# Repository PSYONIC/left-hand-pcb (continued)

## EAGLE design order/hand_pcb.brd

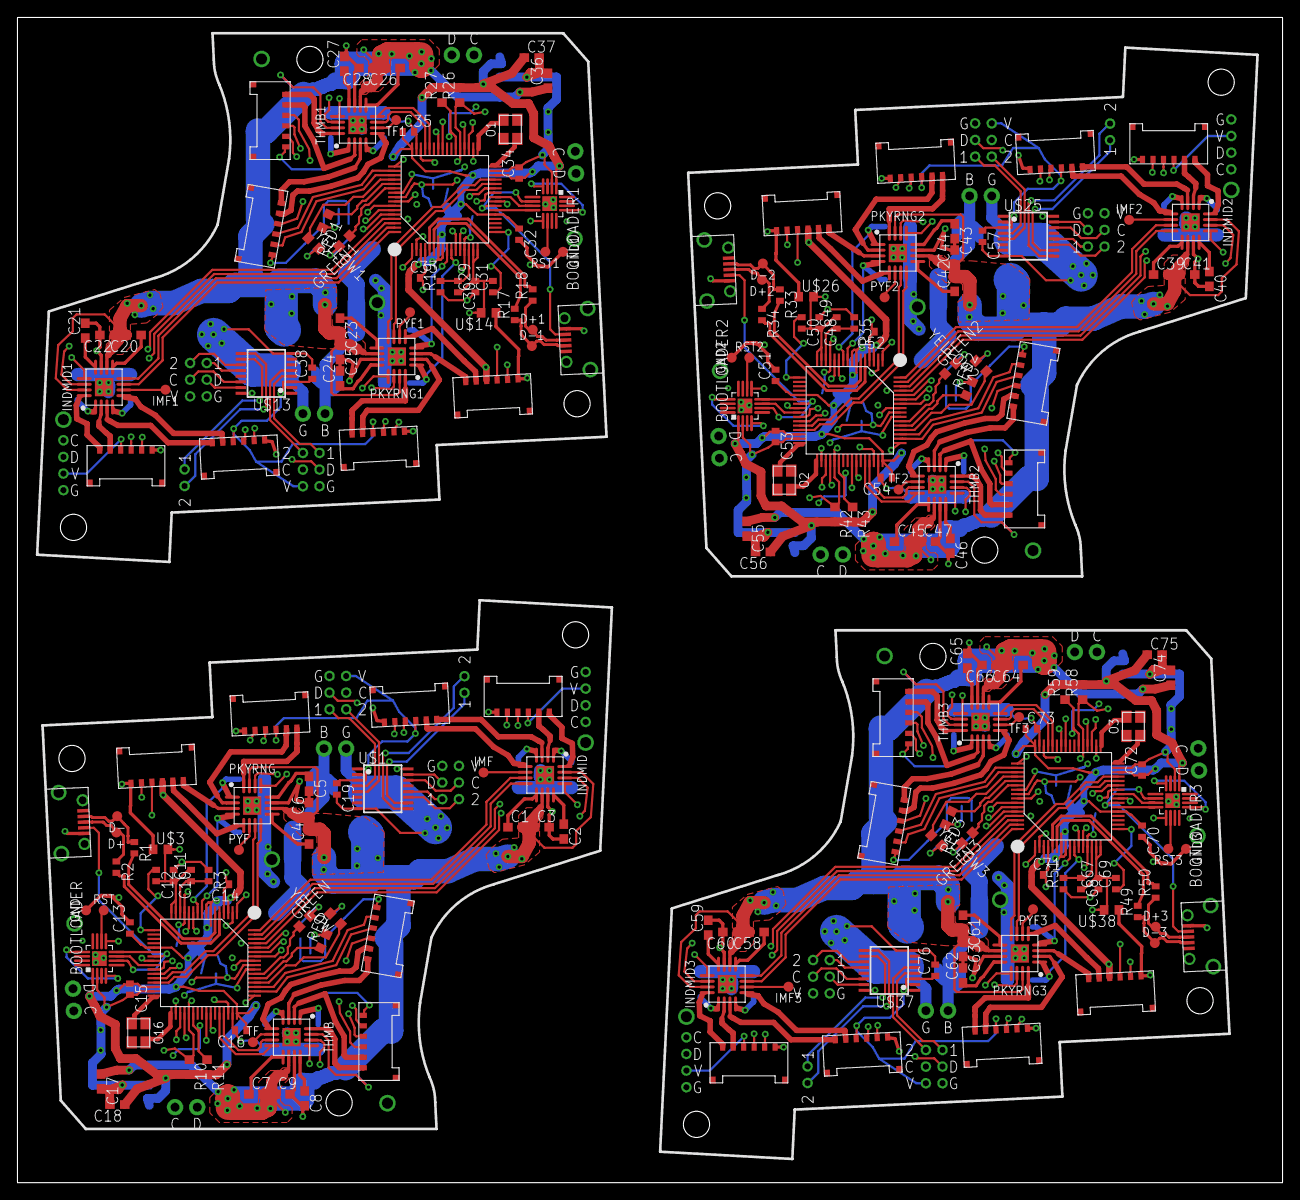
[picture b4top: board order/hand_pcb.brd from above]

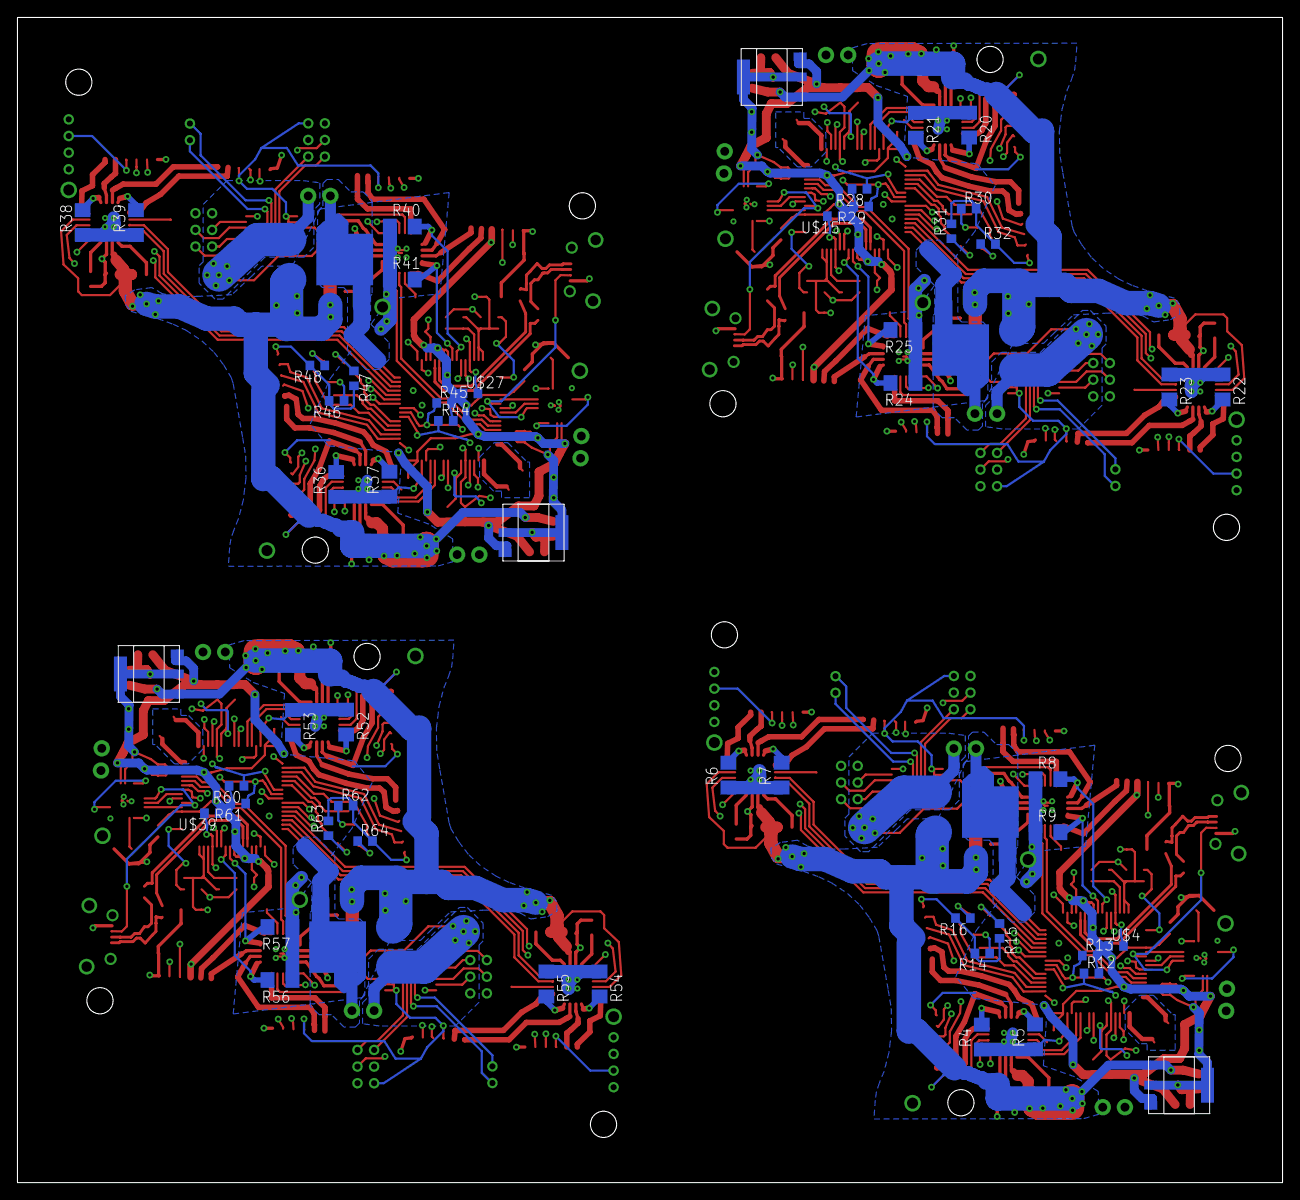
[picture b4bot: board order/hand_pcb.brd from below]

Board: 4 copper layers, 144.8 x 133.3 mm, 280 parts (56 on the bottom side), 348 nets.

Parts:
BOOTLOADER, BOOTLOADER1, BOOTLOADER2, BOOTLOADER3: MKL02Z32CORRECT; QFN16
C1, C4, C7, C20, C23, C26, C39, C42, C45, C58, C61, C64: 0.01; C0603
C2, C5, C8, C21, C24, C27, C40, C43, C46, C59, C62, C65: 2.2; C0603
C3, C6, C9, C22, C25, C28, C41, C44, C47, C60, C63, C66: 10; C0603
C10, C29, C48, C67: 2.2; C0402
C11, C12, C13, C14, C15, C16, C19, C30, C31, C32, C33, C34, C35, C38, C49, C50, C51, C52, C53, C54, C57, C68, C69, C70, C71, C72, C73, C76: 0.1; C0402
C17, C18, C36, C37, C55, C56, C74, C75: C0603
D+, D+1, D+2, D+3: TESTPAD
D-, D-1, D-2, D-3: TESTPAD
GND, GND1, GND2, GND3: TESTPAD
GREEN, GREEN1, GREEN2, GREEN3: LED0603; L0603
HAND_MICRO, HAND_MICRO1, HAND_MICRO2, HAND_MICRO3: MK20DX256VLH7; LQFP-64-10-10
IMF, IMF1, IMF2, IMF3: TESTPAD
INDEX, INDEX1, INDEX2, INDEX3: DF57H-6PTOP; DF57H-6P-TOP
INDMID, INDMID1, INDMID2, INDMID3: DRV8833; WQFN-16
MIDDLE, MIDDLE1, MIDDLE2, MIDDLE3: DF57H-6PTOP; DF57H-6P-TOP
O1, O2, O3, O16: 16MHz; NX3225SA
PINKY, PINKY1, PINKY2, PINKY3: DF57H-6PTOP; DF57H-6P-TOP
PKYRNG, PKYRNG1, PKYRNG2, PKYRNG3: DRV8833; WQFN-16
PYF, PYF1, PYF2, PYF3: TESTPAD
R1, R2, R17, R18, R33, R34, R49, R50: 33; R0402
R3, R19, R35, R51: 470; R0402
R4, R5, R6, R7, R8, R9, R20, R21, R22, R23, R24, R25, R36, R37, R38, R39, R40, R41, R52, R53, R54, R55, R56, R57: 0.2; R1206
R10, R11, R12, R13, R26, R27, R28, R29, R42, R43, R44, R45, R58, R59, R60, R61: 1k; R0603
R14, R30, R46, R62: 100; R0603
R15, R16, R31, R32, R47, R48, R63, R64: 200; R0603
RED, RED1, RED2, RED3: LED0603; L0603
RING, RING1, RING2, RING3: DF57H-6PTOP; DF57H-6P-TOP
RST, RST1, RST2, RST3: TESTPAD
TF, TF1, TF2, TF3: TESTPAD
THMB, THMB1, THMB2, THMB3: DRV8833; WQFN-16
THUMB_A, THUMB_A1, THUMB_A2, THUMB_A3: DF57H-6PTOP; DF57H-6P-TOP
THUMB_B, THUMB_B1, THUMB_B2, THUMB_B3: DF57H-6PTOP; DF57H-6P-TOP
U$1, U$13, U$25, U$37: TCA9534TSSOP; TSSOP16
U$2, U$16, U$28, U$40: SPD15P10PLG; PG-TO-252-3
U$3, U$4, U$14, U$15, U$26, U$27, U$38, U$39: L0603
U$5, U$7, U$17, U$18, U$29, U$30, U$41, U$42: PSENSE
U$6, U$19, U$31, U$43: PSENSE2
U$8, U$20, U$32, U$44: PSENSE4
U$9, U$21, U$33, U$45: MIC391003.3; MIC39100
U$10, U$22, U$34, U$46: THRUHOLE2
U$11, U$12, U$23, U$24, U$35, U$36, U$47, U$48: THRUHOLEI2C
USB, USB1, USB2, USB3: 10118194-0001LF
YELLOW, YELLOW1, YELLOW2, YELLOW3: LED0603; L0603

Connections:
+3V1: BOOTLOADER1.1, C32.1, C33.1, C34.1, C35.1, C37.1, C38.1, HAND_MICRO1.3, HAND_MICRO1.7, HAND_MICRO1.8, HAND_MICRO1.21, HAND_MICRO1.30, HAND_MICRO1.48, INDEX1.3, MIDDLE1.3, PINKY1.3, R26.2, R27.2, R28.2, R29.2, RING1.3, THUMB_A1.3, THUMB_B1.3, U$13.1, U$13.2, U$13.3, U$13.16, U$15.1, U$17.V, U$18.V, U$20.V, U$21.3
+3V2: BOOTLOADER2.1, C51.1, C52.1, C53.1, C54.1, C56.1, C57.1, HAND_MICRO2.3, HAND_MICRO2.7, HAND_MICRO2.8, HAND_MICRO2.21, HAND_MICRO2.30, HAND_MICRO2.48, INDEX2.3, MIDDLE2.3, PINKY2.3, R42.2, R43.2, R44.2, R45.2, RING2.3, THUMB_A2.3, THUMB_B2.3, U$25.1, U$25.2, U$25.3, U$25.16, U$27.1, U$29.V, U$30.V, U$32.V, U$33.3
+3V3: BOOTLOADER.1, C13.1, C14.1, C15.1, C16.1, C18.1, C19.1, HAND_MICRO.3, HAND_MICRO.7, HAND_MICRO.8, HAND_MICRO.21, HAND_MICRO.30, HAND_MICRO.48, INDEX.3, MIDDLE.3, PINKY.3, R10.2, R11.2, R12.2, R13.2, RING.3, THUMB_A.3, THUMB_B.3, U$1.1, U$1.2, U$1.3, U$1.16, U$4.1, U$5.V, U$7.V, U$8.V, U$9.3
+3V4: BOOTLOADER3.1, C70.1, C71.1, C72.1, C73.1, C75.1, C76.1, HAND_MICRO3.3, HAND_MICRO3.7, HAND_MICRO3.8, HAND_MICRO3.21, HAND_MICRO3.30, HAND_MICRO3.48, INDEX3.3, MIDDLE3.3, PINKY3.3, R58.2, R59.2, R60.2, R61.2, RING3.3, THUMB_A3.3, THUMB_B3.3, U$37.1, U$37.2, U$37.3, U$37.16, U$39.1, U$41.V, U$42.V, U$44.V, U$45.3
+5V: C1.2, C3.1, C4.2, C6.1, C7.2, C9.1, C17.1, INDMID.10, INDMID.15, PKYRNG.10, PKYRNG.15, THMB.10, THMB.15, U$2.3, U$9.1
+5V1: C20.2, C22.1, C23.2, C25.1, C26.2, C28.1, C36.1, INDMID1.10, INDMID1.15, PKYRNG1.10, PKYRNG1.15, THMB1.10, THMB1.15, U$16.3, U$21.1
+5V2: C39.2, C41.1, C42.2, C44.1, C45.2, C47.1, C55.1, INDMID2.10, INDMID2.15, PKYRNG2.10, PKYRNG2.15, THMB2.10, THMB2.15, U$28.3, U$33.1
+5V3: C58.2, C60.1, C61.2, C63.1, C64.2, C66.1, C74.1, INDMID3.10, INDMID3.15, PKYRNG3.10, PKYRNG3.15, THMB3.10, THMB3.15, U$40.3, U$45.1
EN1: U$1.4, U$5.1
EN2: U$1.5, U$5.2
EN3: U$1.12, U$7.1
EN4: U$1.11, U$7.2
EN5: U$1.10, U$6.1
EN6: U$1.9, U$6.2
EN7: U$13.4, U$17.1
EN8: U$13.5, U$17.2
EN9: U$13.9, U$19.2
EN10: U$13.12, U$18.1
EN11: U$13.11, U$18.2
EN12: U$13.10, U$19.1
EN13: U$25.4, U$29.1
EN14: U$25.5, U$29.2
EN15: U$25.9, U$31.2
EN16: U$25.12, U$30.1
EN17: U$25.11, U$30.2
EN18: U$25.10, U$31.1
EN19: U$37.4, U$41.1
EN20: U$37.5, U$41.2
EN21: U$37.9, U$43.2
EN22: U$37.12, U$42.1
EN23: U$37.11, U$42.2
EN24: U$37.10, U$43.1
GND: BOOTLOADER.2, BOOTLOADER.TH, C2.2, C3.2, C5.2, C6.2, C8.2, C9.2, C13.2, C14.2, C15.2, C16.2, C17.2, C18.2, C19.2, GND.P$1, HAND_MICRO.4, HAND_MICRO.31, HAND_MICRO.47, INDEX.6, INDMID.11, INDMID.PPAD, MIDDLE.6, PINKY.6, PKYRNG.11, PKYRNG.PPAD, R4.1, R5.1, R6.1, R7.1, R8.1, R9.1, R14.2, R15.2, R16.2, RING.6, THMB.11, THMB.PPAD, THUMB_A.6, THUMB_B.6, U$1.8, U$2.1, U$3.1, U$5.G, U$7.G, U$8.G, U$9.2, U$9.TAB, U$10.G, USB.5
GND1: BOOTLOADER1.2, BOOTLOADER1.TH, C21.2, C22.2, C24.2, C25.2, C27.2, C28.2, C32.2, C33.2, C34.2, C35.2, C36.2, C37.2, C38.2, GND1.P$1, HAND_MICRO1.4, HAND_MICRO1.31, HAND_MICRO1.47, INDEX1.6, INDMID1.11, INDMID1.PPAD, MIDDLE1.6, PINKY1.6, PKYRNG1.11, PKYRNG1.PPAD, R20.1, R21.1, R22.1, R23.1, R24.1, R25.1, R30.2, R31.2, R32.2, RING1.6, THMB1.11, THMB1.PPAD, THUMB_A1.6, THUMB_B1.6, U$13.8, U$14.1, U$16.1, U$17.G, U$18.G, U$20.G, U$21.2, U$21.TAB, U$22.G, USB1.5
GND2: BOOTLOADER2.2, BOOTLOADER2.TH, C40.2, C41.2, C43.2, C44.2, C46.2, C47.2, C51.2, C52.2, C53.2, C54.2, C55.2, C56.2, C57.2, GND2.P$1, HAND_MICRO2.4, HAND_MICRO2.31, HAND_MICRO2.47, INDEX2.6, INDMID2.11, INDMID2.PPAD, MIDDLE2.6, PINKY2.6, PKYRNG2.11, PKYRNG2.PPAD, R36.1, R37.1, R38.1, R39.1, R40.1, R41.1, R46.2, R47.2, R48.2, RING2.6, THMB2.11, THMB2.PPAD, THUMB_A2.6, THUMB_B2.6, U$25.8, U$26.1, U$28.1, U$29.G, U$30.G, U$32.G, U$33.2, U$33.TAB, U$34.G, USB2.5
GND3: BOOTLOADER3.2, BOOTLOADER3.TH, C59.2, C60.2, C62.2, C63.2, C65.2, C66.2, C70.2, C71.2, C72.2, C73.2, C74.2, C75.2, C76.2, GND3.P$1, HAND_MICRO3.4, HAND_MICRO3.31, HAND_MICRO3.47, INDEX3.6, INDMID3.11, INDMID3.PPAD, MIDDLE3.6, PINKY3.6, PKYRNG3.11, PKYRNG3.PPAD, R52.1, R53.1, R54.1, R55.1, R56.1, R57.1, R62.2, R63.2, R64.2, RING3.6, THMB3.11, THMB3.PPAD, THUMB_A3.6, THUMB_B3.6, U$37.8, U$38.1, U$40.1, U$41.G, U$42.G, U$44.G, U$45.2, U$45.TAB, U$46.G, USB3.5
IDX1: INDEX.1, INDMID.16
IDX2: INDEX.2, INDMID.2
IDX3: INDEX1.1, INDMID1.16
IDX4: INDEX1.2, INDMID1.2
IDX5: INDEX2.1, INDMID2.16
IDX6: INDEX2.2, INDMID2.2
IDX7: INDEX3.1, INDMID3.16
IDX8: INDEX3.2, INDMID3.2
IDXENC1: HAND_MICRO.58, INDEX.5
IDXENC2: HAND_MICRO.57, INDEX.4
IDXENC3: HAND_MICRO1.57, INDEX1.4
IDXENC4: HAND_MICRO1.58, INDEX1.5
IDXENC5: HAND_MICRO2.57, INDEX2.4
IDXENC6: HAND_MICRO2.58, INDEX2.5
IDXENC7: HAND_MICRO3.57, INDEX3.4
IDXENC8: HAND_MICRO3.58, INDEX3.5
IDXISEN: INDMID.1, R6.2
IDXISEN1: INDMID1.1, R22.2
IDXISEN2: INDMID2.1, R38.2
IDXISEN3: INDMID3.1, R54.2
IDXPWM1: HAND_MICRO.61, INDMID.14
IDXPWM2: HAND_MICRO.62, INDMID.13
IDXPWM3: HAND_MICRO1.62, INDMID1.13
IDXPWM4: HAND_MICRO1.61, INDMID1.14
IDXPWM5: HAND_MICRO2.62, INDMID2.13
IDXPWM6: HAND_MICRO2.61, INDMID2.14
IDXPWM7: HAND_MICRO3.62, INDMID3.13
IDXPWM8: HAND_MICRO3.61, INDMID3.14
LED0: HAND_MICRO.53, RED.1
LED1: GREEN.1, HAND_MICRO.54
LED2: HAND_MICRO.52, YELLOW.1
LED3: HAND_MICRO1.53, RED1.1
LED4: GREEN1.1, HAND_MICRO1.54
LED5: HAND_MICRO1.52, YELLOW1.1
LED6: HAND_MICRO2.53, RED2.1
LED7: GREEN2.1, HAND_MICRO2.54
LED8: HAND_MICRO2.52, YELLOW2.1
LED9: HAND_MICRO3.53, RED3.1
LED10: GREEN3.1, HAND_MICRO3.54
LED11: HAND_MICRO3.52, YELLOW3.1
MID1: INDMID.5, MIDDLE.2
MID2: INDMID.3, MIDDLE.1
MID3: INDMID1.3, MIDDLE1.1
MID4: INDMID1.5, MIDDLE1.2
MID5: INDMID2.3, MIDDLE2.1
MID6: INDMID2.5, MIDDLE2.2
MID7: INDMID3.3, MIDDLE3.1
MID8: INDMID3.5, MIDDLE3.2
MIDENC1: HAND_MICRO.60, MIDDLE.5
MIDENC2: HAND_MICRO.59, MIDDLE.4
MIDENC3: HAND_MICRO1.59, MIDDLE1.4
MIDENC4: HAND_MICRO1.60, MIDDLE1.5
MIDENC5: HAND_MICRO2.59, MIDDLE2.4
MIDENC6: HAND_MICRO2.60, MIDDLE2.5
MIDENC7: HAND_MICRO3.59, MIDDLE3.4
MIDENC8: HAND_MICRO3.60, MIDDLE3.5
MIDISEN: INDMID.4, R7.2
MIDISEN1: INDMID1.4, R23.2
MIDISEN2: INDMID2.4, R39.2
MIDISEN3: INDMID3.4, R55.2
MIDPWM1: HAND_MICRO.64, INDMID.7
MIDPWM2: HAND_MICRO.63, INDMID.8
MIDPWM3: HAND_MICRO1.63, INDMID1.8
MIDPWM4: HAND_MICRO1.64, INDMID1.7
MIDPWM5: HAND_MICRO2.63, INDMID2.8
MIDPWM6: HAND_MICRO2.64, INDMID2.7
MIDPWM7: HAND_MICRO3.63, INDMID3.8
MIDPWM8: HAND_MICRO3.64, INDMID3.7
unnamed: R14.1, RED.2
unnamed: GREEN.2, R15.1
unnamed: R16.1, YELLOW.2
unnamed: IMF.P$1, INDMID.6
unnamed: PKYRNG.6, PYF.P$1
unnamed: TF.P$1, THMB.6
unnamed: C10.1, HAND_MICRO.13, R3.1, U$4.2
unnamed: BOOTLOADER.9, HAND_MICRO.24
unnamed: C11.1, HAND_MICRO.14, R3.2
unnamed: BOOTLOADER.8, HAND_MICRO.22
unnamed: BOOTLOADER.7, HAND_MICRO.25
unnamed: BOOTLOADER.10, RST.P$1
unnamed: BOOTLOADER1.4, BOOTLOADER1.13, HAND_MICRO1.34
unnamed: C29.2, C30.2, C31.2, HAND_MICRO1.15, HAND_MICRO1.16, U$14.2
unnamed: C20.1, INDMID1.9
unnamed: C23.1, PKYRNG1.9
unnamed: BOOTLOADER.4, BOOTLOADER.13, HAND_MICRO.34
unnamed: C10.2, C11.2, C12.2, HAND_MICRO.15, HAND_MICRO.16, U$3.2
unnamed: C26.1, THMB1.9
unnamed: C27.1, THMB1.12
unnamed: C1.1, INDMID.9
unnamed: C4.1, PKYRNG.9
unnamed: C7.1, THMB.9
unnamed: HAND_MICRO.33, O16.3
unnamed: C8.1, THMB.12
unnamed: C5.1, PKYRNG.12
unnamed: C2.1, INDMID.12
unnamed: HAND_MICRO.32, O16.1
unnamed: C24.1, PKYRNG1.12
unnamed: C21.1, INDMID1.12
unnamed: HAND_MICRO1.33, O1.3
unnamed: HAND_MICRO1.32, O1.1
unnamed: C31.1, HAND_MICRO1.17
unnamed: C12.1, HAND_MICRO.17
unnamed: BOOTLOADER.6, HAND_MICRO.23, USB.4
unnamed: BOOTLOADER1.6, HAND_MICRO1.23, USB1.4
unnamed: R30.1, RED1.2
unnamed: GREEN1.2, R31.1
unnamed: R32.1, YELLOW1.2
unnamed: IMF1.P$1, INDMID1.6
unnamed: PKYRNG1.6, PYF1.P$1
unnamed: TF1.P$1, THMB1.6
unnamed: C29.1, HAND_MICRO1.13, R19.1, U$15.2
unnamed: C30.1, HAND_MICRO1.14, R19.2
unnamed: BOOTLOADER1.9, HAND_MICRO1.24
unnamed: BOOTLOADER1.8, HAND_MICRO1.22
unnamed: BOOTLOADER1.7, HAND_MICRO1.25
unnamed: BOOTLOADER1.10, RST1.P$1
unnamed: BOOTLOADER2.4, BOOTLOADER2.13, HAND_MICRO2.34
unnamed: C48.2, C49.2, C50.2, HAND_MICRO2.15, HAND_MICRO2.16, U$26.2
unnamed: C39.1, INDMID2.9
unnamed: C42.1, PKYRNG2.9
unnamed: C45.1, THMB2.9
unnamed: C46.1, THMB2.12
unnamed: C43.1, PKYRNG2.12
unnamed: C40.1, INDMID2.12
unnamed: HAND_MICRO2.33, O2.3
unnamed: HAND_MICRO2.32, O2.1
unnamed: C50.1, HAND_MICRO2.17
unnamed: BOOTLOADER2.6, HAND_MICRO2.23, USB2.4
unnamed: R46.1, RED2.2
unnamed: GREEN2.2, R47.1
unnamed: R48.1, YELLOW2.2
unnamed: IMF2.P$1, INDMID2.6
unnamed: PKYRNG2.6, PYF2.P$1
unnamed: TF2.P$1, THMB2.6
unnamed: C48.1, HAND_MICRO2.13, R35.1, U$27.2
unnamed: C49.1, HAND_MICRO2.14, R35.2
unnamed: BOOTLOADER2.9, HAND_MICRO2.24
unnamed: BOOTLOADER2.8, HAND_MICRO2.22
unnamed: BOOTLOADER2.7, HAND_MICRO2.25
unnamed: BOOTLOADER2.10, RST2.P$1
unnamed: BOOTLOADER3.4, BOOTLOADER3.13, HAND_MICRO3.34
unnamed: C67.2, C68.2, C69.2, HAND_MICRO3.15, HAND_MICRO3.16, U$38.2
unnamed: C58.1, INDMID3.9
unnamed: C61.1, PKYRNG3.9
unnamed: C64.1, THMB3.9
unnamed: C65.1, THMB3.12
unnamed: C62.1, PKYRNG3.12
unnamed: C59.1, INDMID3.12
unnamed: HAND_MICRO3.33, O3.3
unnamed: HAND_MICRO3.32, O3.1
unnamed: C69.1, HAND_MICRO3.17
unnamed: BOOTLOADER3.6, HAND_MICRO3.23, USB3.4
unnamed: R62.1, RED3.2
unnamed: GREEN3.2, R63.1
unnamed: R64.1, YELLOW3.2
unnamed: IMF3.P$1, INDMID3.6
unnamed: PKYRNG3.6, PYF3.P$1
unnamed: TF3.P$1, THMB3.6
unnamed: C67.1, HAND_MICRO3.13, R51.1, U$39.2
unnamed: C68.1, HAND_MICRO3.14, R51.2
unnamed: BOOTLOADER3.9, HAND_MICRO3.24
unnamed: BOOTLOADER3.8, HAND_MICRO3.22
unnamed: BOOTLOADER3.7, HAND_MICRO3.25
unnamed: BOOTLOADER3.10, RST3.P$1
PKY1: PINKY.2, PKYRNG.5
PKY2: PINKY.1, PKYRNG.3
PKY3: PINKY1.2, PKYRNG1.5
PKY4: PINKY1.1, PKYRNG1.3
PKY5: PINKY2.2, PKYRNG2.5
PKY6: PINKY2.1, PKYRNG2.3
PKY7: PINKY3.2, PKYRNG3.5
PKY8: PINKY3.1, PKYRNG3.3
PKYENC1: HAND_MICRO.26, PINKY.5
PKYENC2: HAND_MICRO.27, PINKY.4
PKYENC3: HAND_MICRO1.26, PINKY1.5
PKYENC4: HAND_MICRO1.27, PINKY1.4
PKYENC5: HAND_MICRO2.26, PINKY2.5
PKYENC6: HAND_MICRO2.27, PINKY2.4
PKYENC7: HAND_MICRO3.26, PINKY3.5
PKYENC8: HAND_MICRO3.27, PINKY3.4
PKYISEN: HAND_MICRO.9, PKYRNG.4, R9.2
PKYISEN1: HAND_MICRO1.9, PKYRNG1.4, R25.2
PKYISEN2: HAND_MICRO2.9, PKYRNG2.4, R41.2
PKYISEN3: HAND_MICRO3.9, PKYRNG3.4, R57.2
PKYPWM1: HAND_MICRO.28, PKYRNG.7
PKYPWM2: HAND_MICRO.29, PKYRNG.8
PKYPWM3: HAND_MICRO1.29, PKYRNG1.8
PKYPWM4: HAND_MICRO1.28, PKYRNG1.7
PKYPWM5: HAND_MICRO2.29, PKYRNG2.8
PKYPWM6: HAND_MICRO2.28, PKYRNG2.7
PKYPWM7: HAND_MICRO3.29, PKYRNG3.8
PKYPWM8: HAND_MICRO3.28, PKYRNG3.7
RNG1: PKYRNG.16, RING.1
RNG2: PKYRNG.2, RING.2
RNG3: PKYRNG1.16, RING1.1
RNG4: PKYRNG1.2, RING1.2
RNG5: PKYRNG2.16, RING2.1
RNG6: PKYRNG2.2, RING2.2
RNG7: PKYRNG3.16, RING3.1
RNG8: PKYRNG3.2, RING3.2
RNGENC1: HAND_MICRO.2, RING.5
RNGENC2: HAND_MICRO.1, RING.4
RNGENC3: HAND_MICRO1.1, RING1.4
RNGENC4: HAND_MICRO1.2, RING1.5
RNGENC5: HAND_MICRO2.1, RING2.4
RNGENC6: HAND_MICRO2.2, RING2.5
RNGENC7: HAND_MICRO3.1, RING3.4
RNGENC8: HAND_MICRO3.2, RING3.5
RNGISEN: HAND_MICRO.10, PKYRNG.1, R8.2
RNGISEN1: HAND_MICRO1.10, PKYRNG1.1, R24.2
RNGISEN2: HAND_MICRO2.10, PKYRNG2.1, R40.2
RNGISEN3: HAND_MICRO3.10, PKYRNG3.1, R56.2
RNGPWM1: HAND_MICRO.46, PKYRNG.14
RNGPWM2: HAND_MICRO.49, PKYRNG.13
RNGPWM3: HAND_MICRO1.49, PKYRNG1.13
RNGPWM4: HAND_MICRO1.46, PKYRNG1.14
RNGPWM5: HAND_MICRO2.49, PKYRNG2.13
RNGPWM6: HAND_MICRO2.46, PKYRNG2.14
RNGPWM7: HAND_MICRO3.49, PKYRNG3.13
RNGPWM8: HAND_MICRO3.46, PKYRNG3.14
SCL0: HAND_MICRO.37, R10.1, U$1.14, U$5.C, U$7.C, U$8.C, U$11.SCL
SCL1: HAND_MICRO.55, R12.1, U$12.SCL
SCL2: HAND_MICRO1.37, R26.1, U$13.14, U$17.C, U$18.C, U$20.C, U$23.SCL
SCL3: HAND_MICRO1.55, R28.1, U$24.SCL
SCL4: HAND_MICRO2.37, R42.1, U$25.14, U$29.C, U$30.C, U$32.C, U$35.SCL
SCL5: HAND_MICRO2.55, R44.1, U$36.SCL
SCL6: HAND_MICRO3.37, R58.1, U$37.14, U$41.C, U$42.C, U$44.C, U$47.SCL
SCL7: HAND_MICRO3.55, R60.1, U$48.SCL
SDA0: HAND_MICRO.38, R11.1, U$1.15, U$5.D, U$7.D, U$8.D, U$11.SDA
SDA1: HAND_MICRO.56, R13.1, U$12.SDA
SDA2: HAND_MICRO1.38, R27.1, U$13.15, U$17.D, U$18.D, U$20.D, U$23.SDA
SDA3: HAND_MICRO1.56, R29.1, U$24.SDA
SDA4: HAND_MICRO2.38, R43.1, U$25.15, U$29.D, U$30.D, U$32.D, U$35.SDA
SDA5: HAND_MICRO2.56, R45.1, U$36.SDA
SDA6: HAND_MICRO3.38, R59.1, U$37.15, U$41.D, U$42.D, U$44.D, U$47.SDA
SDA7: HAND_MICRO3.56, R61.1, U$48.SDA
THA1: THMB.16, THUMB_A.1
THA2: THMB.2, THUMB_A.2
THA3: THMB1.16, THUMB_A1.1
THA4: THMB1.2, THUMB_A1.2
THA5: THMB2.16, THUMB_A2.1
THA6: THMB2.2, THUMB_A2.2
THA7: THMB3.16, THUMB_A3.1
THA8: THMB3.2, THUMB_A3.2
THAENC1: HAND_MICRO.35, THUMB_A.5
THAENC2: HAND_MICRO.36, THUMB_A.4
THAENC3: HAND_MICRO1.36, THUMB_A1.4
THAENC4: HAND_MICRO1.35, THUMB_A1.5
THAENC5: HAND_MICRO2.36, THUMB_A2.4
THAENC6: HAND_MICRO2.35, THUMB_A2.5
THAENC7: HAND_MICRO3.36, THUMB_A3.4
THAENC8: HAND_MICRO3.35, THUMB_A3.5
THAISEN: HAND_MICRO.11, R4.2, THMB.1
THAISEN1: HAND_MICRO1.11, R20.2, THMB1.1
THAISEN2: HAND_MICRO2.11, R36.2, THMB2.1
THAISEN3: HAND_MICRO3.11, R52.2, THMB3.1
THAPWM1: HAND_MICRO.41, THMB.14
THAPWM2: HAND_MICRO.42, THMB.13
THAPWM3: HAND_MICRO1.42, THMB1.13
THAPWM4: HAND_MICRO1.41, THMB1.14
THAPWM5: HAND_MICRO2.42, THMB2.13
THAPWM6: HAND_MICRO2.41, THMB2.14
THAPWM7: HAND_MICRO3.42, THMB3.13
THAPWM8: HAND_MICRO3.41, THMB3.14
THB1: THMB.5, THUMB_B.2
THB2: THMB.3, THUMB_B.1
THB3: THMB1.3, THUMB_B1.1
THB4: THMB1.5, THUMB_B1.2
THB5: THMB2.3, THUMB_B2.1
THB6: THMB2.5, THUMB_B2.2
THB7: THMB3.3, THUMB_B3.1
THB8: THMB3.5, THUMB_B3.2
THBENC1: HAND_MICRO.51, THUMB_B.5
THBENC2: HAND_MICRO.50, THUMB_B.4
THBENC3: HAND_MICRO1.50, THUMB_B1.4
THBENC4: HAND_MICRO1.51, THUMB_B1.5
THBENC5: HAND_MICRO2.50, THUMB_B2.4
THBENC6: HAND_MICRO2.51, THUMB_B2.5
THBENC7: HAND_MICRO3.50, THUMB_B3.4
THBENC8: HAND_MICRO3.51, THUMB_B3.5
THBISEN: HAND_MICRO.12, R5.2, THMB.4
THBISEN1: HAND_MICRO1.12, R21.2, THMB1.4
THBISEN2: HAND_MICRO2.12, R37.2, THMB2.4
THBISEN3: HAND_MICRO3.12, R53.2, THMB3.4
THBPWM1: HAND_MICRO.45, THMB.7
THBPWM2: HAND_MICRO.44, THMB.8
THBPWM3: HAND_MICRO1.44, THMB1.8
THBPWM4: HAND_MICRO1.45, THMB1.7
THBPWM5: HAND_MICRO2.44, THMB2.8
THBPWM6: HAND_MICRO2.45, THMB2.7
THBPWM7: HAND_MICRO3.44, THMB3.8
THBPWM8: HAND_MICRO3.45, THMB3.7
USB_D1_N: D-.P$1, R1.1, USB.2
USB_D1_N1: D-1.P$1, R17.1, USB1.2
USB_D1_N2: D-2.P$1, R33.1, USB2.2
USB_D1_N3: D-3.P$1, R49.1, USB3.2
USB_D1_P: D+.P$1, R2.1, USB.3
USB_D1_P1: D+1.P$1, R18.1, USB1.3
USB_D1_P2: D+2.P$1, R34.1, USB2.3
USB_D1_P3: D+3.P$1, R50.1, USB3.3
USB_D2_N: HAND_MICRO.6, R1.2
USB_D2_N1: HAND_MICRO1.6, R17.2
USB_D2_N2: HAND_MICRO2.6, R33.2
USB_D2_N3: HAND_MICRO3.6, R49.2
USB_D2_P: HAND_MICRO.5, R2.2
USB_D2_P1: HAND_MICRO1.5, R18.2
USB_D2_P2: HAND_MICRO2.5, R34.2
USB_D2_P3: HAND_MICRO3.5, R50.2
VIN: U$2.2, U$10.B
VIN1: U$16.2, U$22.B
VIN2: U$28.2, U$34.B
VIN3: U$40.2, U$46.B

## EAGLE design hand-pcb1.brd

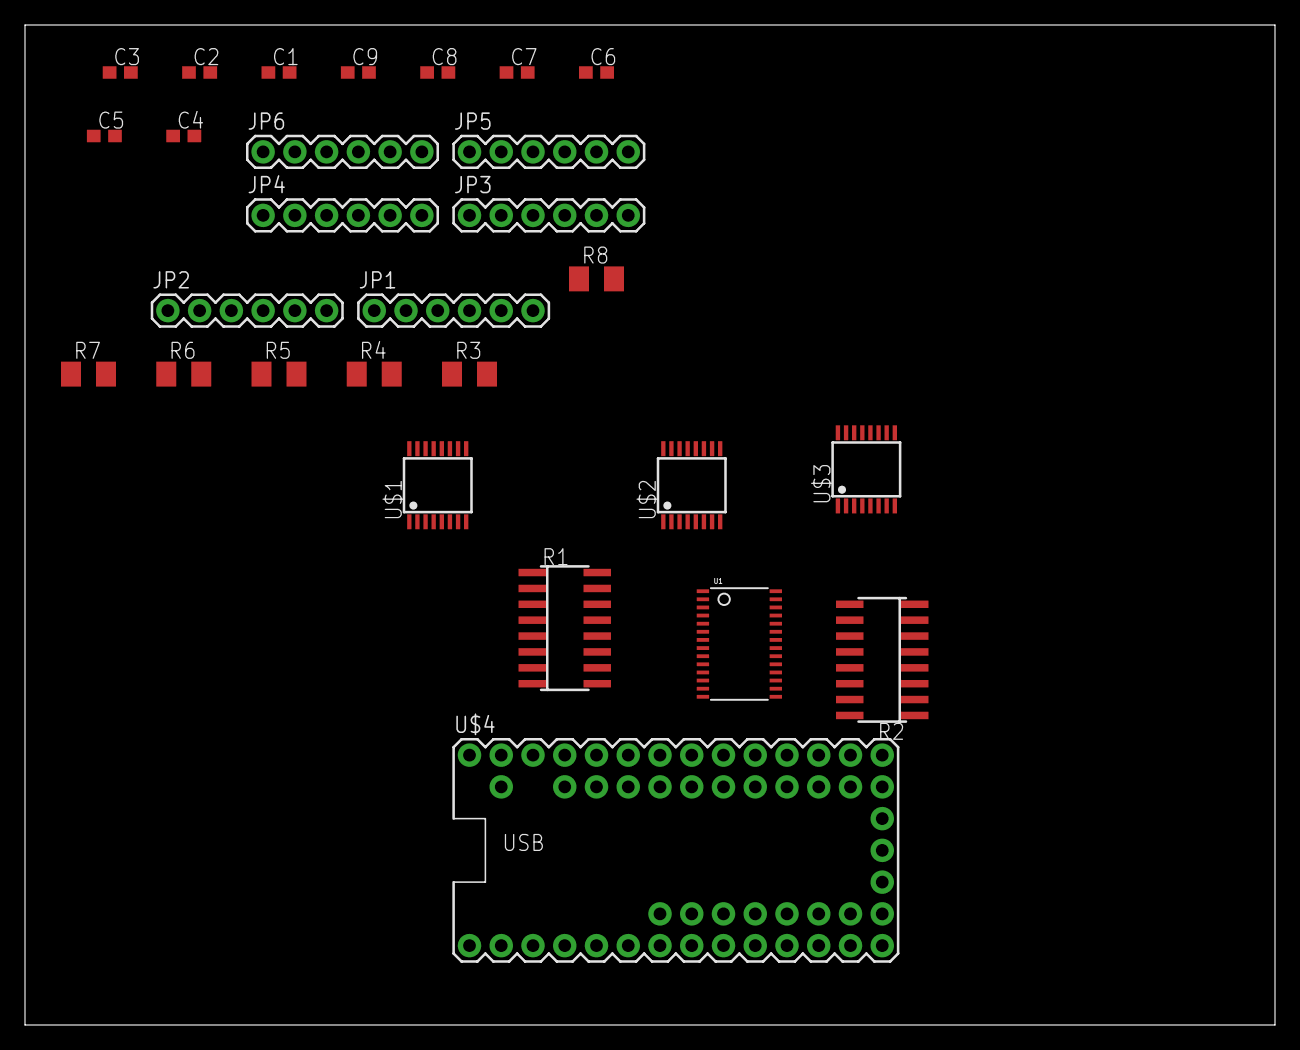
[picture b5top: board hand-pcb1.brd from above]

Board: 2 copper layers, 100.0 x 80.0 mm, 28 parts (0 on the bottom side), 54 nets, no tracks yet.

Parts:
C1, C2, C3: 10uF; C0603
C4, C5, C6: 2.2uF; C0603
C7, C8, C9: .01uF; C0603
JP1, JP2, JP3, JP4, JP5, JP6: 1X06
R1, R2: SO16
R3, R4, R5, R6, R7, R8: 0.15Ω; M1206
U1: TSSOP28
U$1, U$2, U$3: DRV8833; TSSOP16
U$4: TEENSY32

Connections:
+3V3: JP1.4, JP2.4, JP3.4, JP4.4, JP5.4, JP6.4, U$4.3VB, U$4.3VM, U$4.3VT, U$4.AREF
GND: C1.2, C2.2, C3.2, C4.2, C5.2, C6.2, JP1.1, JP2.1, JP3.1, JP4.1, JP5.1, JP6.1, R3.2, R4.2, R5.2, R6.2, R7.2, R8.2, U1.14, U1.25, U$1.1, U$1.13, U$2.1, U$2.13, U$3.1, U$3.13, U$4.AGND, U$4.GNDB, U$4.GNDM, U$4.GNDT
ME11: JP1.2, U$4.D0
ME12: JP1.3, U$4.D1
ME21: JP2.2, U$4.D2
ME22: JP2.3, U$4.D3
ME31: JP3.2, U$4.D4
ME32: JP3.3, U$4.D5
ME41: JP4.2, U$4.D6
ME51: JP5.2, U$4.D8
ME52: JP5.3, U$4.D9
ME61: JP6.2, U$4.D10
ME62: JP6.3, U$4.D11
MP11: JP1.5, U$1.2
MP12: JP1.6, U$1.4
MP21: JP2.5, U$1.7
MP22: JP2.6, U$1.5
MP31: JP3.5, U$2.2
MP32: JP3.6, U$2.4
MP41: JP4.5, U$2.7
MP42: JP4.6, U$2.5
MP51: JP5.5, U$3.2
MP52: JP5.6, U$3.4
MP61: JP6.5, U$3.7
MP62: JP6.6, U$3.5
MS1: R3.1, U$1.3, U$4.A13
MS2: R4.1, U$1.6, U$4.A11
MS3: R5.1, U$2.3, U$4.A10
MS4: R6.1, U$2.6, U$4.D28
MS5: R7.1, U$3.3, U$4.D27
MS6: R8.1, U$3.6, U$4.D26
unnamed: R1.9, U1.13
unnamed: R1.10, U1.12
unnamed: R1.11, U1.11
unnamed: R1.12, U1.10
unnamed: R1.13, U1.9
unnamed: R1.14, U1.8
unnamed: R1.15, U1.7
unnamed: R1.16, U1.6
unnamed: R2.9, U1.22
unnamed: R2.10, U1.21
unnamed: R2.11, U1.20
unnamed: R2.12, U1.19
unnamed: R2.13, U1.18
unnamed: R2.14, U1.17
unnamed: R2.15, U1.16
unnamed: R2.16, U1.15
unnamed: C4.1, U$1.14
unnamed: C5.1, U$2.14
unnamed: C6.1, U$3.14
SCL: U1.26, U$4.D19
SDA: U1.27, U$4.D18
V+: C7.1, C8.1, C9.1, U1.28, U$1.11, U$2.11, U$3.11
VM: C1.1, C2.1, C3.1, C7.2, C8.2, C9.2, U$1.12, U$2.12, U$3.12

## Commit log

2016-04-06 files and libraries for pcb
2016-04-06 added testpads for error pins on motor drivers
2016-04-06 added .1uF cap for io expander for stability - not fully needed but good practice
2016-04-06 updated library component for motor connector
2016-04-06 corrected some resistors and caps for the M04
2016-04-06 qfn package for bootloader
2016-04-06 fixed bootloader
2016-04-06 added order info
2016-05-20 cleaning up repo - removing extra files
2016-05-20 updated capacitor values for bypass caps to 10u, cleaned up schematic, updated tanalum cap value for linear regulator
2016-05-20 removing extra files
2016-05-20 moving files into place
2016-05-20 added ignores for cam files and temp backups
2016-05-20 importing files from right hand
